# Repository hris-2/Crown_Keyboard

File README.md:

# CROWN KEYBOARD
A simple 6 by 5 split keyboard with 3 thumb keys and a display.  
It is planned to be made through Ergogen, KiCad and ZMK.  
This not complete yet or fully tested so please do not use yet.  

## Features
As meationed before it is 6x5 with thumb keys all multiplied by 2 so 66 keys.  
It uses a Nice!Nano v2 so it has wireless and wired capability.  
Along with the Nice!Nano it has Nice!View for the display.  
The keyboard will include a reset button and a battery slider too.  
It will not be reverisble but can eaily bcome by removing mirrored sections and addin reversible tags to areas  

## Which Ergogen
I have been using https://ergogen.ceoloide.com the unoffical web version.  
Because it includes ability to add custom footprints there is no need for downloading it.  
For this reason all the inputs and outputs in the Ergogen folder aren't sorted like they would be on the local version.  
I would recommened this to people who are going for simpler designs.  
My footprints that I use are taken from Christian Selig.  

## Unusual Elements
Unlike most people I used outlines and combos for the mounting points intead of footprints in pcbs.  
I did this so i could visually see them in ergogen to stop the amount of times i had to switch between Ergogen and KiCad.  
It also has stilts for the pcb to sit on so i have room for the battery and maybe have foam or something to provide a bit more support. 

# THIS IS NOT FINISHED DO NOT USE YET PLEASE

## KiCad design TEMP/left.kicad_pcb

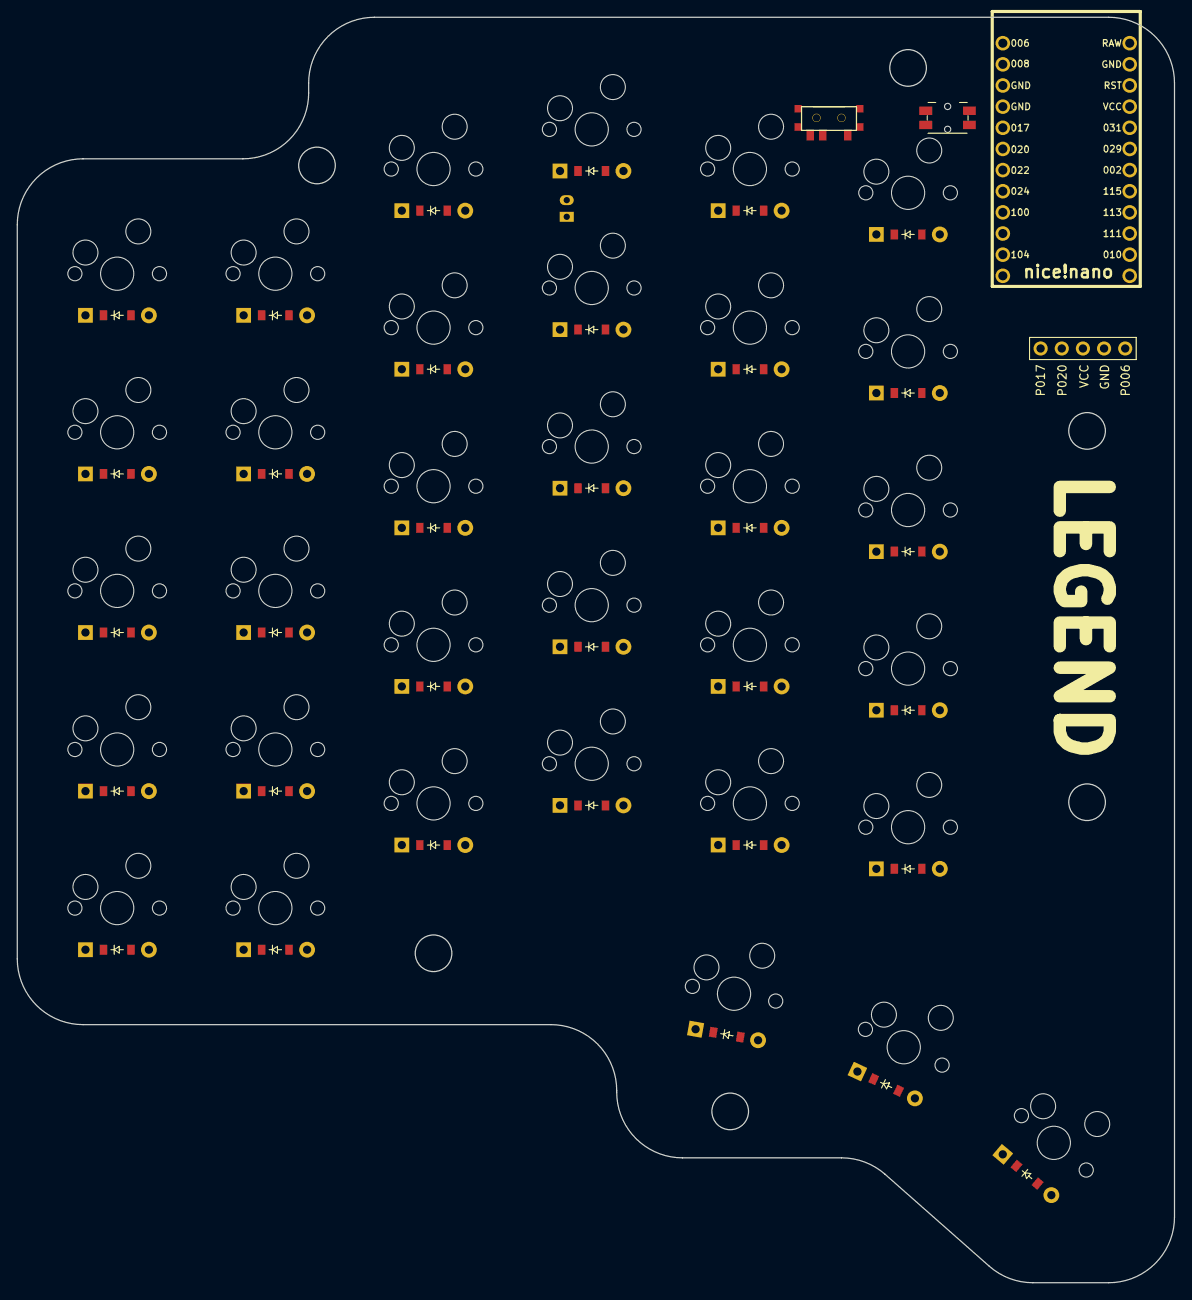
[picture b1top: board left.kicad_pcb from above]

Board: 2 copper layers, 139.0 x 152.0 mm, 71 parts (0 on the bottom side), 53 nets, no tracks yet.

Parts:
B1: Panasonic_EVQPUL_EVQPUC
D1, D2, D3, D4, D5, D6, D7, D8, D9, D10, D11, D12, D13, D14, D15, D16, D17, D18, D19, D20, D21, D22, D23, D24, D25, D26, D27, D28, D29, D30, D31, D32, D33: ComboDiode
DISP1: display_nice_view
JST1: JST_PH_S2B-PH-K_02x2.00mm_Angled
MCU1: nice_nano
S1, S2, S3, S4, S5, S6, S7, S8, S9, S10, S11, S12, S13, S14, S15, S16, S17, S18, S19, S20, S21, S22, S23, S24, S25, S26, S27, S28, S29, S30, S31, S32, S33: MX
T1: SPDT_C128955

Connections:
GND: B1.1, DISP1.4, JST1.2, MCU1.3, MCU1.4, MCU1.23
P006: DISP1.5, MCU1.1
P017: DISP1.1, MCU1.5
P020: DISP1.2, MCU1.6
RAW: MCU1.24, T1.2
RST: B1.2, MCU1.22
VCC: DISP1.3, MCU1.21
col_1: MCU1.7, S26.1, S27.1, S28.1, S29.1, S30.1, S33.1
col_2: MCU1.8, S21.1, S22.1, S23.1, S24.1, S25.1, S32.1
col_3: MCU1.10, S16.1, S17.1, S18.1, S19.1, S20.1, S31.1
col_4: MCU1.9, S11.1, S12.1, S13.1, S14.1, S15.1
col_5: MCU1.11, S6.1, S7.1, S8.1, S9.1, S10.1
col_6: MCU1.12, S1.1, S2.1, S3.1, S4.1, S5.1
in_default: D31.2, S31.2
index_bottom: D22.2, S22.2
index_control: D21.2, S21.2
index_home: D23.2, S23.2
index_num: D25.2, S25.2
index_top: D24.2, S24.2
inner_bottom: D27.2, S27.2
inner_control: D26.2, S26.2
inner_home: D28.2, S28.2
inner_num: D30.2, S30.2
inner_top: D29.2, S29.2
mid_default: D32.2, S32.2
middle_bottom: D17.2, S17.2
middle_control: D16.2, S16.2
middle_home: D18.2, S18.2
middle_num: D20.2, S20.2
middle_top: D19.2, S19.2
out_default: D33.2, S33.2
outer_bottom: D2.2, S2.2
outer_control: D1.2, S1.2
outer_home: D3.2, S3.2
outer_num: D5.2, S5.2
outer_top: D4.2, S4.2
pinky_bottom: D7.2, S7.2
pinky_control: D6.2, S6.2
pinky_home: D8.2, S8.2
pinky_num: D10.2, S10.2
pinky_top: D9.2, S9.2
pos: JST1.1, T1.1
ring_bottom: D12.2, S12.2
ring_control: D11.2, S11.2
ring_home: D13.2, S13.2
ring_num: D15.2, S15.2
ring_top: D14.2, S14.2
row_1: D5.1, D10.1, D15.1, D20.1, D25.1, D30.1, MCU1.13
row_2: D4.1, D9.1, D14.1, D19.1, D24.1, D29.1, MCU1.14
row_3: D3.1, D8.1, D13.1, D18.1, D23.1, D28.1, MCU1.15
row_4: D2.1, D7.1, D12.1, D17.1, D22.1, D27.1, MCU1.16
row_5: D1.1, D6.1, D11.1, D16.1, D21.1, D26.1, MCU1.17
thumb_1: D31.1, D32.1, D33.1, MCU1.18

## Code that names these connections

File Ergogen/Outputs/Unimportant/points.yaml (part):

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    autobind: 10
    skip: false
    asym: both
    colrow: pinky_control
    name: matrix_pinky_control
    column_net: col_5
    row_net: row_5
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    autobind: 10
    skip: false
    asym: both
    colrow: pinky_bottom
    name: matrix_pinky_bottom
    column_net: col_5
    row_net: row_4
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    autobind: 10
    skip: false
    asym: both
    colrow: pinky_home
    name: matrix_pinky_home
    column_net: col_5
    row_net: row_3
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    autobind: 10
    skip: false
    asym: both
    colrow: pinky_top
    name: matrix_pinky_top
    column_net: col_5
    row_net: row_2
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    autobind: 10
    skip: false
    asym: both
    colrow: pinky_num
    name: matrix_pinky_num
    column_net: col_5
    row_net: row_1
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
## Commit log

2025-05-28 Create TEMP to Create Ergogen Folder
2025-05-28 Create TEMP to Create Outputs
2025-05-28 Create TEMP to Create KiCad
2025-05-28 Create TEMP to Create Gerber
2025-05-28 Create TEMP to Create Inputs
2025-05-28 Create TEMP to Create Footprints
2025-05-28 Create TEMP to Create ZMK
2025-05-28 Create TEMP to Create Footprints to Correct Mistake
2025-05-28 Move left.kicad_pcb to Ergogen/Outputs/left.kicad_pcb
2025-05-28 Move right.kicad_pcb to Ergogen/Outputs/right.kicad_pcb
2025-05-28 Create TEMP to Create Inputs to Corect Mistake
2025-05-28 Create TEMP to Create Footprints to Correct Mistakes
2025-05-29 Add text.js
2025-05-29 Add nice_nano.js
2025-05-29 Add evqpuc.js
2025-05-29 Create TEMP to Create Unimportant
2025-05-29 Move canonical.yaml Ergogen/Outputs/Unimportant to Ergogen/Outputs
2025-05-29 Move demo.dfx Ergogen/Outputs/Unimportant to Ergogen/Outputs
2025-05-29 Rename Ergogen/Outputs/Unimportant/keys_all.dxf to Ergogen/Outputs/keys_all.dxf
2025-05-29 Rename Ergogen/Outputs/Unimportant/left_keys.dxf to Ergogen/Outputs/left_keys.dxf
2025-05-29 Rename Ergogen/Outputs/Unimportant/units.yaml to Ergogen/Outputs/units.yaml
2025-05-29 Rename Ergogen/Outputs/Unimportant/right_keys.dxf to Ergogen/Outputs/right_keys.dxf
2025-05-29 Rename Ergogen/Outputs/Unimportant/raw.txt to Ergogen/Outputs/raw.txt
2025-05-29 Rename Ergogen/Outputs/Unimportant/raw.dxf to Ergogen/Outputs/raw.dxf
2025-05-29 Rename Ergogen/Outputs/Unimportant/points.yaml to Ergogen/Outputs/points.yaml
2025-05-29 Create TEMP to Create Case & KeyCaps
2025-05-29 Create TEMP to Creat Outlines
2025-05-29 Create TEMP to Create Cases
2025-05-29 Rename Ergogen/Outputs/both_combo.dxf to Ergogen/Outputs/Outlines/both_combo.dxf
2025-05-29 Rename Ergogen/Outputs/keys_all.dxf to Ergogen/Outputs/Outlines/keys_all.dxf
2025-05-29 Rename Ergogen/Outputs/demo.dxf to Ergogen/Outputs/Outlines/demo.dxf
2025-05-29 Rename Ergogen/Outputs/left_board.dxf to Ergogen/Outputs/Outlines/left_board.dxf
2025-05-29 Rename Ergogen/Outputs/left_combo.dxf to Ergogen/Outputs/Outlines/left_combo.dxf
2025-05-29 Rename Ergogen/Outputs/left_pcb.dxf to Ergogen/Outputs/Outlines/left_pcb.dxf
2025-05-29 Rename Ergogen/Outputs/left_keys.dxf to Ergogen/Outputs/Outlines/left_keys.dxf
2025-05-29 Rename Ergogen/Outputs/right_xlboard.dxf to Ergogen/Outputs/Outlines/right_xlboard.dxf
2025-05-29 Rename Ergogen/Outputs/right_stlits_w_holes.dxf to Ergogen/Outputs/Outlines/right_stlits_w_holes.dxf
2025-05-29 Rename Ergogen/Outputs/right_stilts.dxf to Ergogen/Outputs/Outlines/right_stilts.dxf
2025-05-29 Rename Ergogen/Outputs/left_mounting_holes.dxf to Ergogen/Outputs/Outlines/left_mounting_holes.dxf
2025-05-29 Rename Ergogen/Outputs/left_stilts.dxf to Ergogen/Outputs/Outlines/left_stilts.dxf
2025-05-29 Rename Ergogen/Outputs/left_stilts_w_holes.dxf to Ergogen/Outputs/Outlines/left_stilts_w_holes.dxf
2025-05-29 Rename Ergogen/Outputs/right_keys.dxf to Ergogen/Outputs/Outlines/right_keys.dxf
2025-05-29 Rename Ergogen/Outputs/left_niceview_template.dxf to Ergogen/Outputs/Outlines/left_niceview_template.dxf
2025-05-29 Rename Ergogen/Outputs/left_xlboard.dxf to Ergogen/Outputs/Outlines/left_xlboard.dxf
2025-05-29 Rename Ergogen/Outputs/raw.dxf to Ergogen/Outputs/Outlines/raw.dxf
2025-05-29 Rename Ergogen/Outputs/right_board.dxf to Ergogen/Outputs/Outlines/right_board.dxf
2025-05-29 Rename Ergogen/Outputs/right_pcb.dxf to Ergogen/Outputs/Outlines/right_pcb.dxf
2025-05-29 Rename Ergogen/Outputs/right_combo.dxf to Ergogen/Outputs/Outlines/right_combo.dxf
2025-05-29 Rename Ergogen/Outputs/right_mounting_holes.dxf to Ergogen/Outputs/Outlines/right_mounting_holes.dxf
2025-05-29 Rename Ergogen/Outputs/right_niceview_template.dxf to Ergogen/Outputs/Outlines/right_niceview_template.dxf
2025-05-29 Rename Ergogen/Outputs/left_bottom.jscad to Ergogen/Outputs/Cases/left_bottom.jscad
2025-05-29 Rename Ergogen/Outputs/left_bottom_case.jscad to Ergogen/Outputs/Cases/left_bottom_case.jscad
2025-05-29 Rename Ergogen/Outputs/left_pcb.jscad to Ergogen/Outputs/Cases/left_pcb.jscad
2025-05-29 Rename Ergogen/Outputs/left_stilts+holes.jscad to Ergogen/Outputs/Cases/left_stilts+holes.jscad
2025-05-29 Rename Ergogen/Outputs/left_top_case.jscad to Ergogen/Outputs/Cases/left_top_case.jscad
2025-05-29 Rename Ergogen/Outputs/right_bottom.jscad to Ergogen/Outputs/Cases/right_bottom.jscad
2025-05-29 Rename Ergogen/Outputs/right_bottom_case.jscad to Ergogen/Outputs/Cases/right_bottom_case.jscad
2025-05-29 Rename Ergogen/Outputs/right_pcb.jscad to Ergogen/Outputs/Cases/right_pcb.jscad
2025-05-29 Rename Ergogen/Outputs/right_stilts+holes.jscad to Ergogen/Outputs/Cases/right_stilts+holes.jscad
2025-05-29 Rename Ergogen/Outputs/right_top_case.jscad to Ergogen/Outputs/Cases/right_top_case.jscad
2025-05-29 Rename Ergogen/Outputs/right_walls.jscad to Ergogen/Outputs/Cases/right_walls.jscad
2025-06-02 Create TEMP to Create TEST
2025-06-04 Rename evqpuc.js to EVQPUC.js to aline with my Ergogen
2025-06-04 Update config.yaml with minor changes and fixes
2025-06-04 Add raw.txt adn right and left .kicad_pcb files to match changes in config.yaml
2025-06-05 Add "h_ris" to Company Section in left.kicad_pcb
2025-06-05 Add "h_ris" to Company Section in right.kicad_pcb
2025-06-16 Create TeMP
2025-06-16 Rename left.kicad_pcb to left2.kicad_pcb
